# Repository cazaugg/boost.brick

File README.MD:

# Readme of boost.brick PCB

## Project description

This is battery holder with a boost regulator that allow generating a voltage of 3.3V or 5V (or any other voltage from 1.8 to 5.5V) from a singel AA cell (NIMH rechargeable compatible).

## Workflow and project organization

- [PCB design and part libraries](pcb/pcb-info.md)
- [Documentation](pcb/doc-info.md)
- [Production](pcb/prod-info.md)

## Tools

Made with KiCad 7. Project setup with [kicad-template-wizard](https://gitlab.com/christoph.zaugg/kicad-template-repo/-/blob/master/script/kicad-wizard.md)

***(c) 2024 by cazaugg***

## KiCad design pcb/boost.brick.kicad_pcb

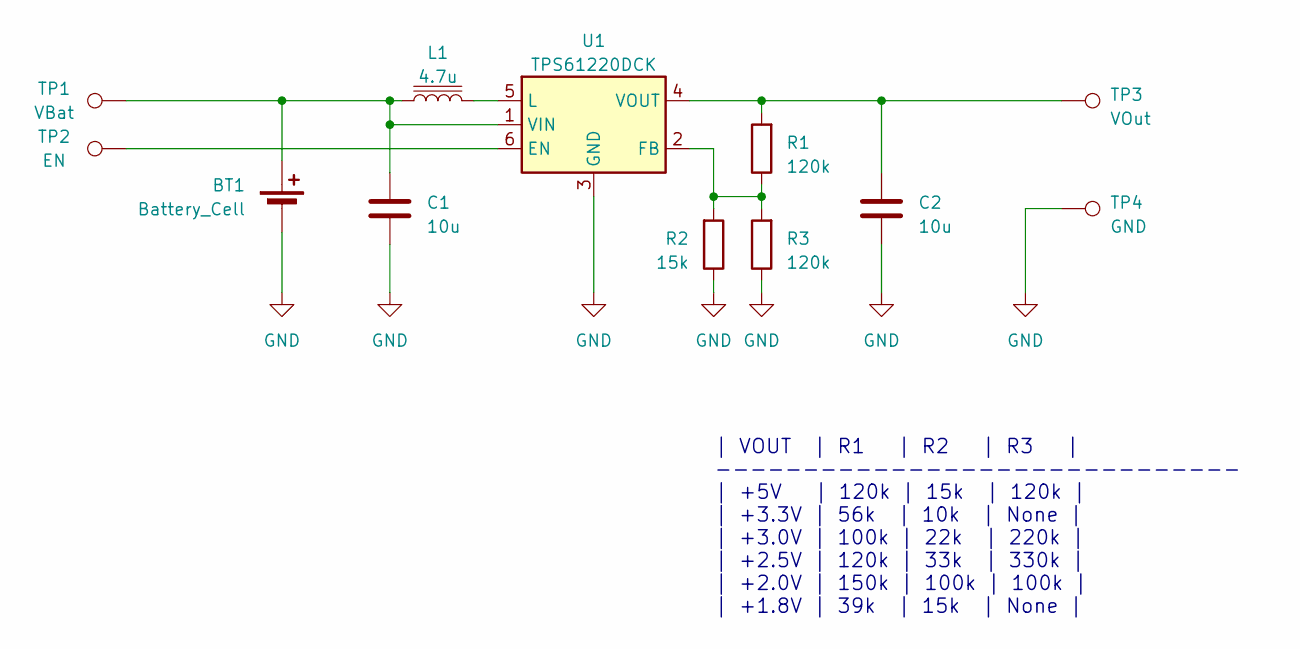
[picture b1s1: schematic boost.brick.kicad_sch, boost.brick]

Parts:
BT1: Battery_Cell; BatteryHolder_Keystone_2460_1xAA
C1, C2: 10u; C_0805_2012Metric
L1: 4.7u; L_Taiyo-Yuden_NR-30xx
R1, R3: 120k; R_0805_2012Metric
R2: 15k; R_0805_2012Metric
TP1: VBat; TestPoint_THTPad_D2.0mm_Drill1.0mm
TP2: EN; TestPoint_THTPad_D2.0mm_Drill1.0mm
TP3: VOut; TestPoint_THTPad_D3.0mm_Drill1.5mm
TP4: GND; TestPoint_THTPad_D3.0mm_Drill1.5mm
U1: TPS61220DCK; Texas_R-PDSO-G6

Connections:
GND: BT1.2 (-), C1.2, C2.2, R2.1, R3.1, TP4.1, U1.3 (GND)
unnamed: BT1.1 (+), C1.1, L1.1, TP1.1, U1.1 (VIN)
unnamed: TP2.1, U1.6 (EN)
unnamed: R1.1, R2.2, R3.2, U1.2 (FB)
unnamed: L1.2, U1.5 (L)
unnamed: C2.1, R1.2, TP3.1, U1.4 (VOUT)

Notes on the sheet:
| VOUT | R1 | R2 | R3 | ------------------------------ | +5V | 120k | 15k | 120k | | +3.3V | 56k | 10k | None | | +3.0V | 100k | 22k | 220k | | +2.5V | 120k | 33k | 330k | | +2.0V | 150k | 100k | 100k | | +1.8V | 39k | 15k | None |

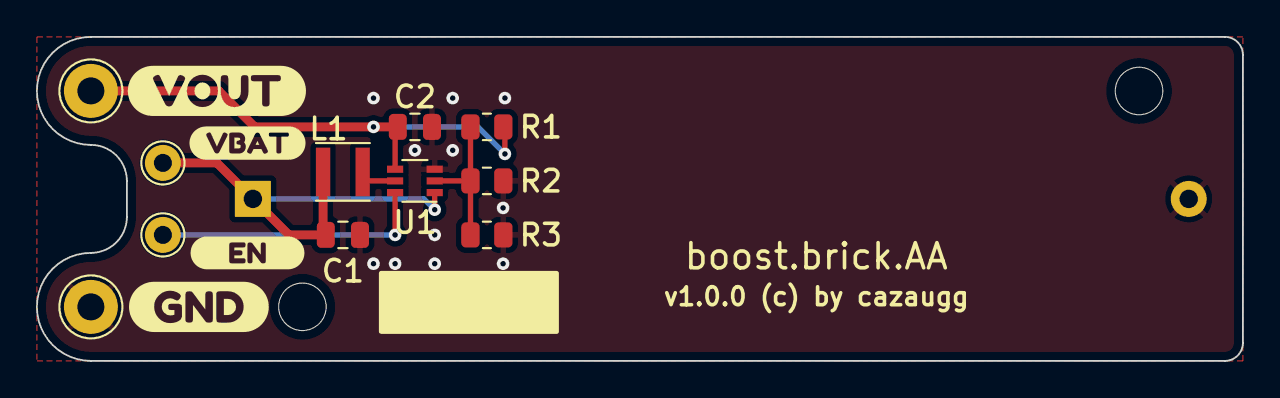
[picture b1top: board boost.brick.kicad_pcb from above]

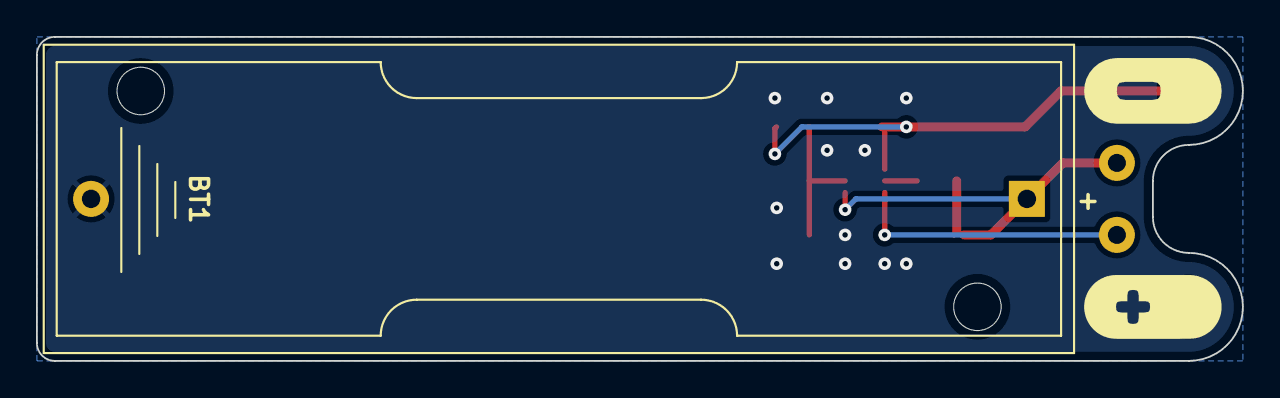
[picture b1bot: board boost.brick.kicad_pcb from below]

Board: 2 copper layers, 67.0 x 18.0 mm, 18 parts (3 on the bottom side), 6 nets.

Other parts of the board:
kibuzzard-64C6B99F: G***; kibuzzard-64C6B99F
kibuzzard-64C6B850: G***; kibuzzard-64C6B850
kibuzzard-64C6BA9D: G***; kibuzzard-64C6BA9D
kibuzzard-64C6BAA4: G***; kibuzzard-64C6BAA4
kibuzzard-64ECEE1E: G***; kibuzzard-64ECEE1E
kibuzzard-64ECEE9B: G***; kibuzzard-64ECEE9B

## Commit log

2023-07-20 Setup repo.
2024-01-01 Add first prototype
2024-01-01 Fix readme
